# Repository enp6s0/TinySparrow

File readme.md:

# TinySparrow
A compact, low(ish)-cost, CAN-FD enabled *core board* for all sorts of automotive shenanigans (and beyond)!

Ever wanted to integrate CAN bus functionality into your projects, but didn't want to
deal with laying out all the commonly used parts every single time?

Then TinySparrow is for you! Now in its 2nd generation, this cute little board combines a
[STM32G0X1](https://www.st.com/en/microcontrollers-microprocessors/stm32g0x1.html) MCU,
2x CAN-FD transceivers and power regulation all in a single board, ready to be integrated
in all your CAN-enabled device ideas.

### General specifications

* Compact footprint: `32 x 27 mm`

* QFN-48 **STM32G0x1** series ARM Cortex-M0+ microcontroller
	* Ships with [STM32G0B1CBU6](https://www.st.com/en/microcontrollers-microprocessors/stm32g0b1cb.html) by default (128K flash, 144K RAM)
	* Also compatible with [STM32G0C1CEU6](https://www.st.com/en/microcontrollers-microprocessors/stm32g0c1ce.html) should you want more RAM/flash or hardware crypto
	* Crystal-less USB device capability

* Dual CAN-FD (up to 5Mbps)
	* Texas Instruments [TCAN332G](https://www.ti.com/product/TCAN332G) PHYs
	* CAN bus ESD diodes included (probably a good idea to add another near connectors though)

* 2-stage automotive power supply
	* Much wider input range: 5 to 25 VDC in!
	* "Batteries included" protection: reverse polarity and voltage clamping diodes onboard
	* **3.3 VDC system voltage** (~500mA available for extra peripherals)
	* Texas Instruments [LMR43610-Q1](https://www.ti.com/product/LMR43610-Q1) buck converter (first stage)
	* STMicroelectronics [LD49100](https://www.st.com/resource/en/datasheet/ld49100.pdf) linear regulator (second stage)

* 2.54mm "pin grid array" I/O connectors
	* 72 total pins available, 61 currently used (all unused MCU pins available)
	* 11 pins reserved for future use (with other boards/revisions)
	* Easy to solder / design carrier boards for :)

### Module pinout

* Top left corner identified by golden notch
* Pins marked with `x` are reserved for future use (do not connect)

|              |              |             |        |        |        |        |     |     |     |            |            |
|:------------:|:------------:|:-----------:|:------:|:------:|:------:|:------:|:---:|:---:|:---:|:----------:|:----------:|
| Key (no pin) |      GND     |     GND     |    x   |    x   |    x   |    x   | GND |  x  |  x  |      x     |  GND       |
|     PA10     |  USB+ (PA12) | USB- (PA11) | CAN0 H | CAN0 L | CAN1 H | CAN1 L | GND |  x  |  x  |      x     | PB14       |
| nRESET (PF2) |  +3V3 (PROG) |             |        |        |        |        |     |     |     |    PB13    | PB12       |
| SWCLK (PA14) | SWDIO (PA13) |             |        |        |        |        |     |     |     |    PB11    | PB10       |
|      PD2     |     PA15     |             |        |        |        |        |     |     |     |     GND    |  PB2       |
|      PB3     |      PD3     |             |        |        |        |        |     |     |     |    PB15    |  PA8       |
|      PB4     |      PB5     |             |        |        |        |        |     |     |     |     PA9    |  PC6       |
|      PB6     |      PB7     |             |        |        |        |        |     |     |     | Power good |  PC7       |
|      PB8     |      PB9     |     PC13    |  PC15  |  +3V3  |   PF1  |   PA1  | PA3 | PA5 | PA7 |      x     |  GND       |
|      GND     |      GND     |     PC14    |  +VBAT |  +3V3  |   PF0  |   PA0  | PA2 | PA4 | PA6 |     GND    |  +VDC (in) |

### Revision/stepping info

* `A1`: initial release for Gen2 design
* `A2`: ESD diode routing fixes, lighter application of via-in-pad to improve manufacturability *(Breaking pinout change: SWDIO/SWCLK swap, +VDC in moved)*

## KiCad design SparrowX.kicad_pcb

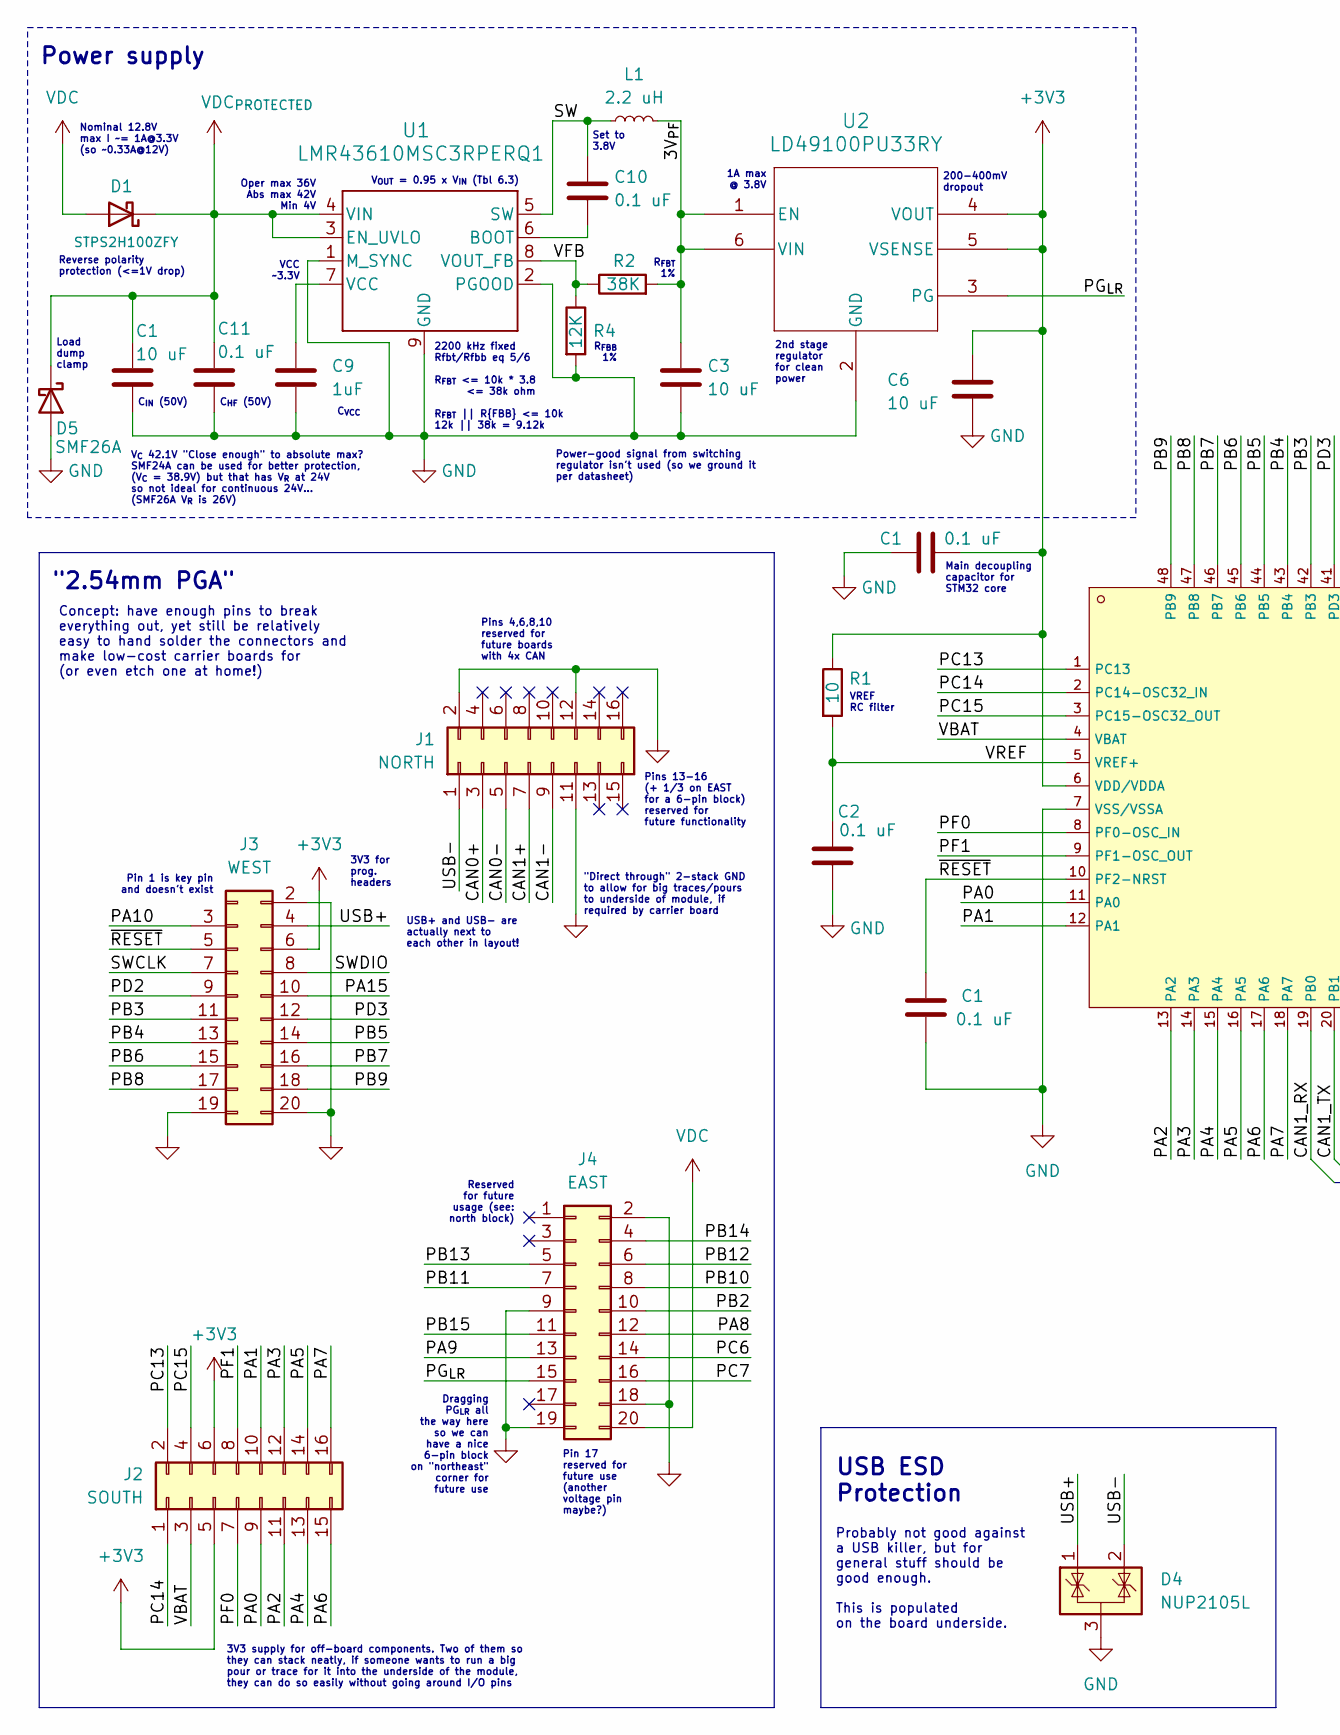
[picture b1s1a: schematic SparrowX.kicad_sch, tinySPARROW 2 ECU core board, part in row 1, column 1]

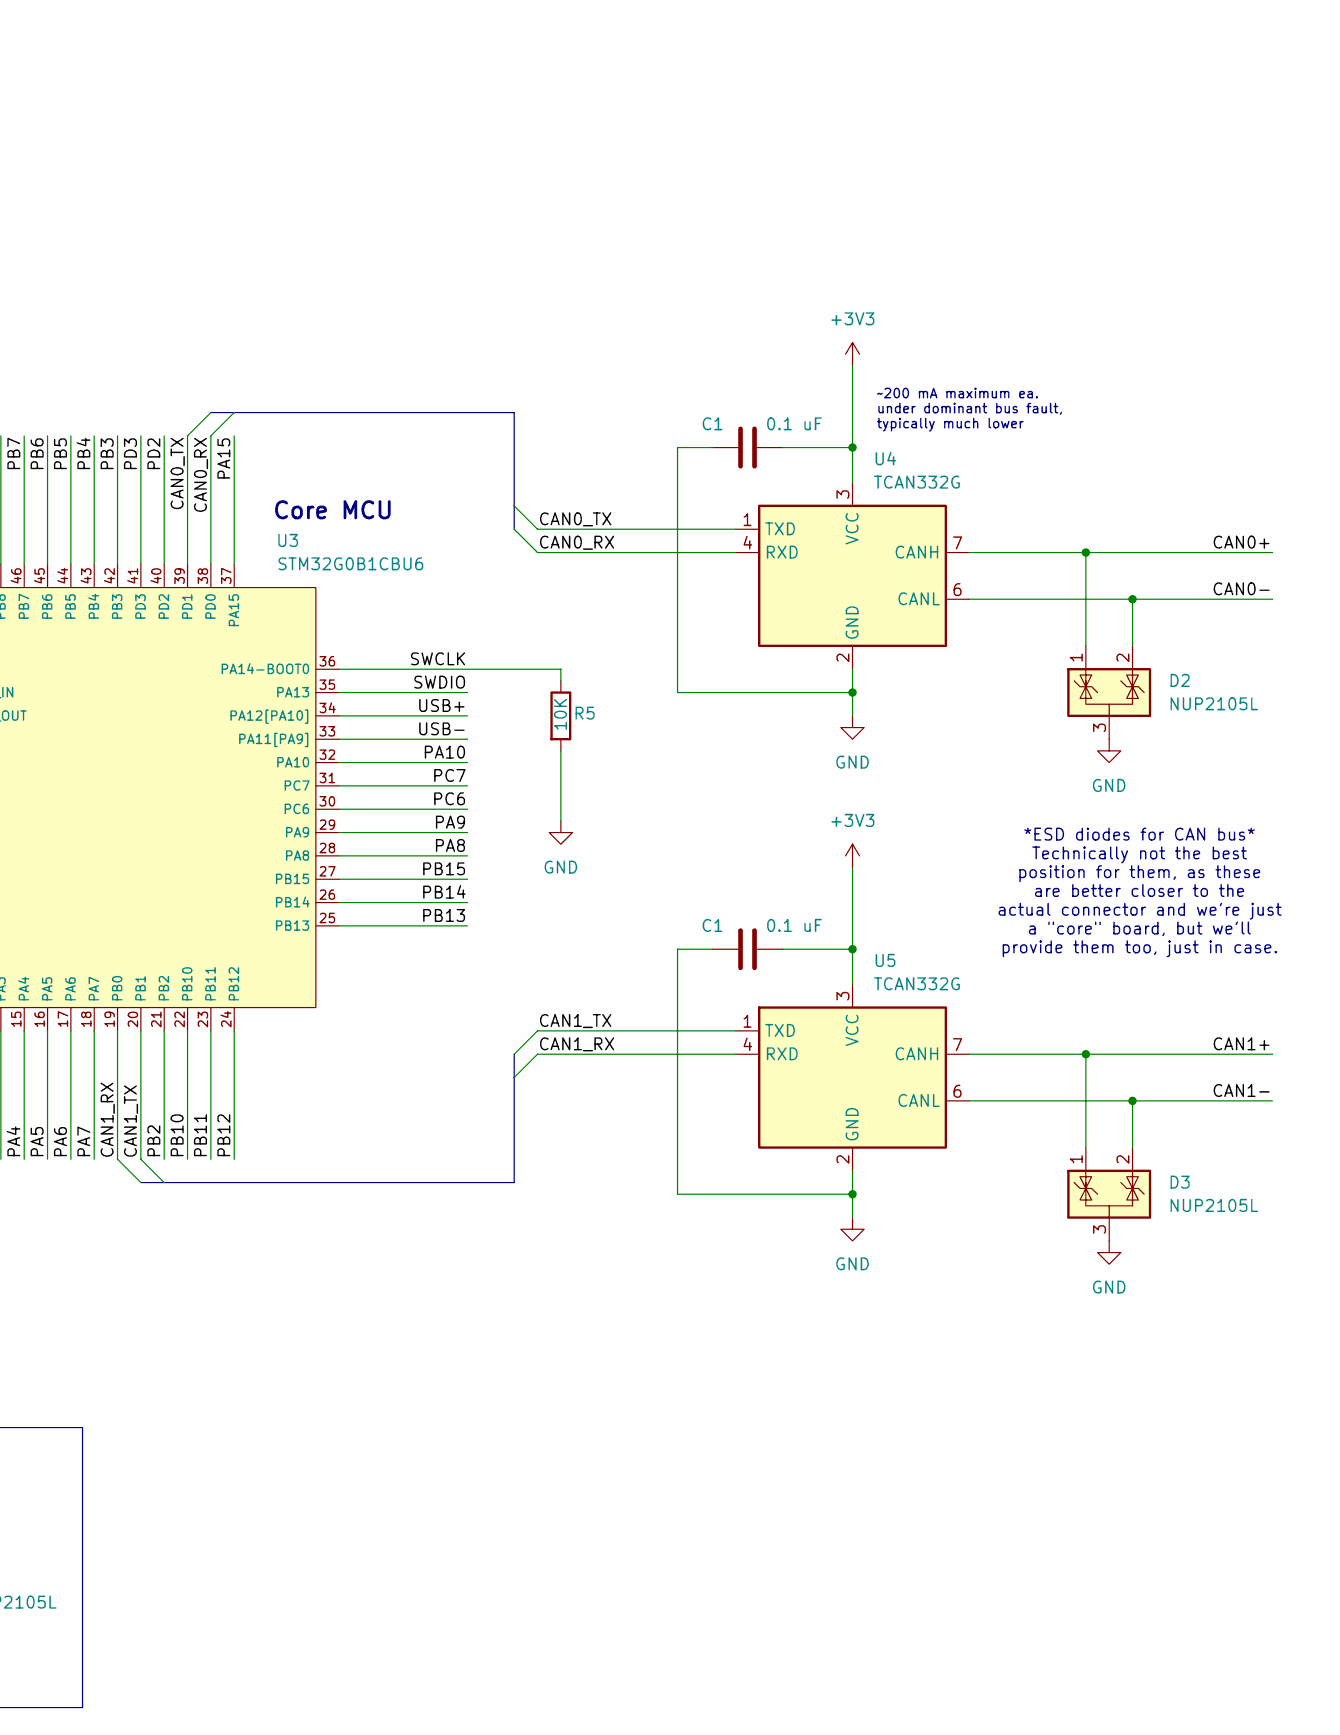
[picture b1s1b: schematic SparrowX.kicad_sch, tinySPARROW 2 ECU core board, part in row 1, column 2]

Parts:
C1, C2, C10, C11: 0.1 uF; C_0402_1005Metric
C3: 10 uF; C_0402_1005Metric; LCSC C377773
C6: 10 uF; C_0805_2012Metric; LCSC C377773
C9: 1uF; C_0402_1005Metric
D1: STPS2H100ZFY; D_SOD-123F
D2, D3, D4: NUP2105L; SOT-23
D5: SMF26A; D_SOD-123F
J1: NORTH; PinHeader_2x08_P2.54mm_Vertical
J2: SOUTH; PinHeader_2x08_P2.54mm_Vertical
J3: WEST; PinHeader_2x10_P2.54mm_Vertical
J4: EAST; PinHeader_2x10_P2.54mm_Vertical
L1: 2.2 uH; L_0805_2012Metric
R1: 10; R_0402_1005Metric
R2: 38K; R_0402_1005Metric
R4: 12K; R_0402_1005Metric
R5: 10K; R_0402_1005Metric
U1: LMR43610MSC3RPERQ1; RPE0009A-MFG
U2: LD49100PU33RY; DFN6_LD49100_STM
U3: STM32G0B1CBU6; QFN-48-1EP_7x7mm_P0.5mm_EP5.6x5.6mm; LCSC C2847904
U4, U5: TCAN332G; SOT-23-8

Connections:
/3V_{PF}: C3.1, L1.2, R2.2, U2.1 (EN), U2.6 (VIN)
/CAN0+: D2.1 (K), J1.3, U4.7 (CANH)
/CAN0-: D2.2 (K), J1.5, U4.6 (CANL)
/CAN0_RX: U3.38 (PD0), U4.4 (RXD)
/CAN0_TX: U3.39 (PD1), U4.1 (TXD)
/CAN1+: D3.1 (K), J1.7, U5.7 (CANH)
/CAN1-: D3.2 (K), J1.9, U5.6 (CANL)
/CAN1_RX: U3.19 (PB0), U5.4 (RXD)
/CAN1_TX: U3.20 (PB1), U5.1 (TXD)
/PA0: J2.9, U3.11 (PA0)
/PA1: J2.10, U3.12 (PA1)
/PA2: J2.11, U3.13 (PA2)
/PA3: J2.12, U3.14 (PA3)
/PA4: J2.13, U3.15 (PA4)
/PA5: J2.14, U3.16 (PA5)
/PA6: J2.15, U3.17 (PA6)
/PA7: J2.16, U3.18 (PA7)
/PA8: J4.12, U3.28 (PA8)
/PA9: J4.13, U3.29 (PA9)
/PA10: J3.3, U3.32 (PA10)
/PA15: J3.10, U3.37 (PA15)
/PB2: J4.10, U3.21 (PB2)
/PB3: J3.11, U3.42 (PB3)
/PB4: J3.13, U3.43 (PB4)
/PB5: J3.14, U3.44 (PB5)
/PB6: J3.15, U3.45 (PB6)
/PB7: J3.16, U3.46 (PB7)
/PB8: J3.17, U3.47 (PB8)
/PB9: J3.18, U3.48 (PB9)
/PB10: J4.8, U3.22 (PB10)
/PB11: J4.7, U3.23 (PB11)
/PB12: J4.6, U3.24 (PB12)
/PB13: J4.5, U3.25 (PB13)
/PB14: J4.4, U3.26 (PB14)
/PB15: J4.11, U3.27 (PB15)
/PC6: J4.14, U3.30 (PC6)
/PC7: J4.16, U3.31 (PC7)
/PC13: J2.2, U3.1 (PC13)
/PC14: J2.1, U3.2 (PC14-OSC32_IN)
/PC15: J2.4, U3.3 (PC15-OSC32_OUT)
/PD2: J3.9, U3.40 (PD2)
/PD3: J3.12, U3.41 (PD3)
/PF0: J2.7, U3.8 (PF0-OSC_IN)
/PF1: J2.8, U3.9 (PF1-OSC_OUT)
/PG_{LR}: J4.15, U2.3 (PG)
/SW: C10.2, L1.1, U1.5 (SW)
/SWCLK: J3.7, R5.1, U3.36 (PA14-BOOT0)
/SWDIO: J3.8, U3.35 (PA13)
/USB+: D4.1 (K), J3.4, U3.34 (PA12[PA10])
/USB-: D4.2 (K), J1.1, U3.33 (PA11[PA9])
/VBAT: J2.3, U3.4 (VBAT)
/VFB: R2.1, R4.1, U1.8 (VOUT_FB)
/VREF: C2.1, R1.2, U3.5 (VREF+)
GND: C1.2, C2.2, C3.2, C6.2, C9.2, C11.2, D2.3 (A), D3.3 (A), D4.3 (A), D5.2 (A), J1.2, J1.11, J1.12, J3.2, J3.19, J3.20, J4.2, J4.9, J4.18, J4.19, R4.2, R5.2, U1.1 (M_SYNC), U1.2 (PGOOD), U1.9 (GND), U2.2 (GND), U2.7 (EPAD), U3.7 (VSS/VSSA), U3.49 (GND_PAD), U4.2 (GND), U5.2 (GND); also elsewhere on the board
unnamed: C10.1, U1.6 (BOOT)
unnamed: C9.1, U1.7 (VCC)
VDC: D1.2 (A), J4.20

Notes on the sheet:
1A max @ 3.8V
Main decoupling capacitor for STM32 core
2200 kHz fixed Rfbt/Rfbb eq 5/6 R_{FBT} <= 10k * 3.8 <= 38k ohm R_{FBT} || R{FBB} <= 10k 12k || 38k = 9.12k
"Direct through" 2-stack GND to allow for big traces/pours to underside of module, if required by carrier board
VCC ~3.3V
~200 mA maximum ea. under dominant bus fault, typically much lower
2nd stage regulator for clean power
Pin 17 reserved for future use (another voltage pin maybe?)
Concept: have enough pins to break everything out, yet still be relatively easy to hand solder the connectors and make low-cost carrier boards for (or even etch one at home!)
Power-good signal from switching regulator isn't used (so we ground it per datasheet)
R_{FBB} 1%
V_{C} 42.1V "Close enough" to absolute max? SMF24A can be used for better protection, (V_{C} = 38.9V) but that has V_{R} at 24V so not ideal for continuous 24V... (SMF26A V_{R} is 26V)
VREF RC filter
Power supply
Set to 3.8V
USB ESD Protection
*ESD diodes for CAN bus* Technically not the best position for them, as these are better closer to the actual connector and we're just a "core" board, but we'll provide them too, just in case.
Load dump clamp
Dragging PG_{LR} all the way here so we can have a nice 6-pin block on "northeast" corner for future use
3V3 for prog. headers
Reverse polarity protection (<=1V drop)
200-400mV dropout
Pins 13-16 (+ 1/3 on EAST for a 6-pin block) reserved for future functionality
Core MCU
"2.54mm PGA"
Probably not good against a USB killer, but for general stuff should be good enough. This is populated on the board underside.
Pin 1 is key pin and doesn't exist
R_{FBT} 1%
USB+ and USB- are actually next to each other in layout!
Pins 4,6,8,10 reserved for future boards with 4x CAN
Nominal 12.8V max I ~= 1A@3.3V (so ~0.33A@12V)
C_{HF} (50V)
Reserved for future usage (see: north block)
3V3 supply for off-board components. Two of them so they can stack neatly, if someone wants to run a big pour or trace for it into the underside of the module, they can do so easily without going around I/O pins
V_{OUT} = 0.95 x V_{IN} (Tbl 6.3)
C_{IN} (50V)
C_{VCC}
Oper max 36V Abs max 42V Min 4V

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
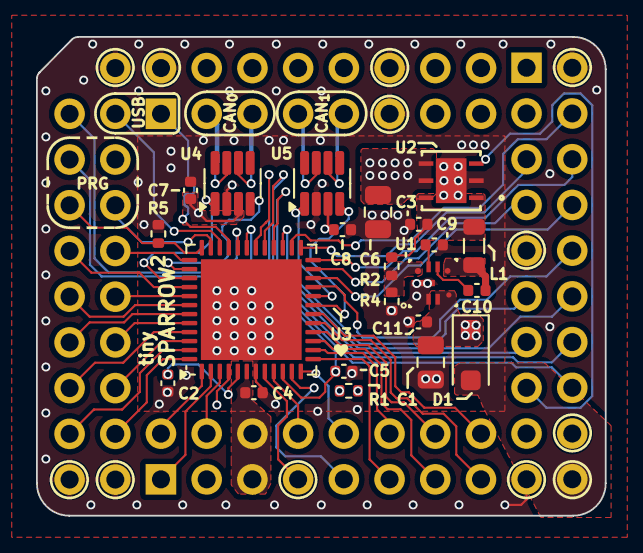
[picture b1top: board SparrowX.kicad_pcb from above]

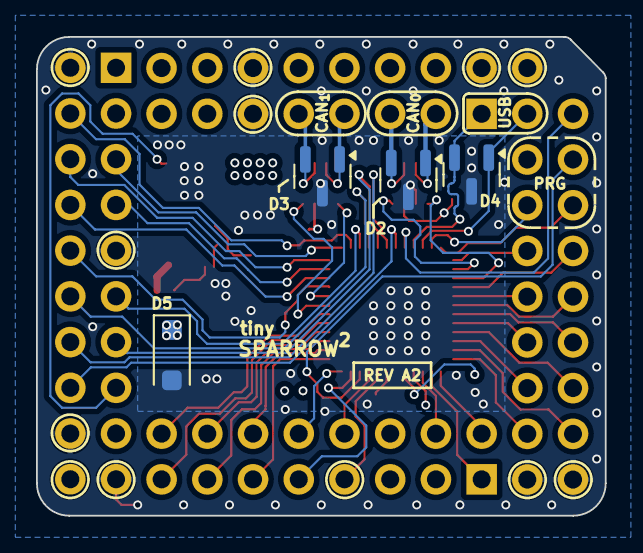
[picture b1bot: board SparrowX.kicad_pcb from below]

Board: 4 copper layers, 31.6 x 26.6 mm, 30 parts (4 on the bottom side), 60 nets.

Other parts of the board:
C4, C5, C7, C8: 0.1 uF; C_0402_1005Metric

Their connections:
GND: C4.2, C5.2, C7.2, C8.2; also elsewhere on the board

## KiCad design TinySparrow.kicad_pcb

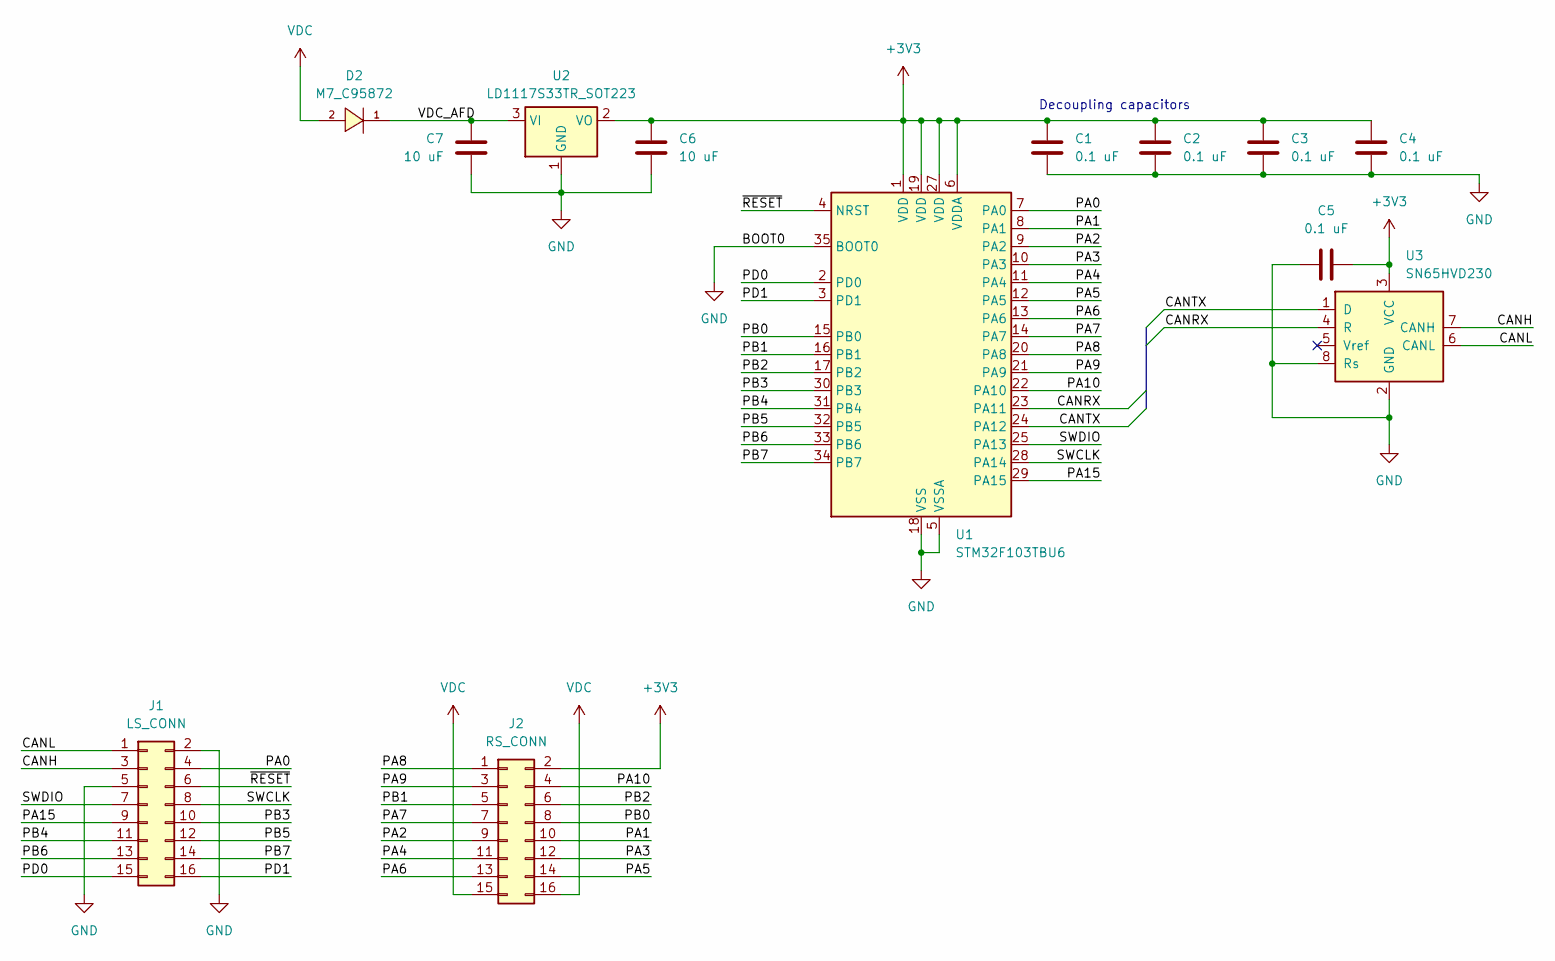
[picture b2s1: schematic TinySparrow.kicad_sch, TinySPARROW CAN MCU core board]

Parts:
C1, C2, C3, C4, C5: 0.1 uF; C_0603_1608Metric
C6: 10 uF; C_0805_2012Metric; LCSC C377773
C7: 10 uF; C_0805_2012Metric
D2: M7_C95872; SMA_L4.3-W2.6-LS5.2-RD; LCSC C95872
J1: LS_CONN; PinSocket_2x08_P2.54mm_Vertical
J2: RS_CONN; PinSocket_2x08_P2.54mm_Vertical
U1: STM32F103TBU6; QFN-36-1EP_6x6mm_P0.5mm_EP4.1x4.1mm
U2: LD1117S33TR_SOT223; SOT-223-3_TabPin2; LCSC C71121
U3: SN65HVD230; SOIC-8_3.9x4.9mm_P1.27mm

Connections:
+3V3: C1.2, C2.2, C3.2, C4.2, C5.1, C6.1, J2.2, U1.1 (VDD), U1.6 (VDDA), U1.19 (VDD), U1.27 (VDD), U2.2 (VO), U3.3 (VCC)
/CANH: J1.3, U3.7 (CANH)
/CANL: J1.1, U3.6 (CANL)
/CANRX: U1.23 (PA11), U3.4 (R)
/CANTX: U1.24 (PA12), U3.1 (D)
/PA0: J1.4, U1.7 (PA0)
/PA1: J2.10, U1.8 (PA1)
/PA2: J2.9, U1.9 (PA2)
/PA3: J2.12, U1.10 (PA3)
/PA4: J2.11, U1.11 (PA4)
/PA5: J2.14, U1.12 (PA5)
/PA6: J2.13, U1.13 (PA6)
/PA7: J2.7, U1.14 (PA7)
/PA8: J2.1, U1.20 (PA8)
/PA9: J2.3, U1.21 (PA9)
/PA10: J2.4, U1.22 (PA10)
/PA15: J1.9, U1.29 (PA15)
/PB0: J2.8, U1.15 (PB0)
/PB1: J2.5, U1.16 (PB1)
/PB2: J2.6, U1.17 (PB2)
/PB3: J1.10, U1.30 (PB3)
/PB4: J1.11, U1.31 (PB4)
/PB5: J1.12, U1.32 (PB5)
/PB6: J1.13, U1.33 (PB6)
/PB7: J1.14, U1.34 (PB7)
/PD0: J1.15, U1.2 (PD0)
/PD1: J1.16, U1.3 (PD1)
/SWCLK: J1.8, U1.28 (PA14)
/SWDIO: J1.7, U1.25 (PA13)
/VDC_AFD: C7.2, U2.3 (VI); also elsewhere on the board
/~RESET: J1.6, U1.4 (NRST)
GND: C1.1, C2.1, C3.1, C4.1, C5.2, C6.2, C7.1, J1.2, J1.5, U1.5 (VSSA), U1.18 (VSS), U1.26 (VSS), U1.35 (BOOT0), U1.36 (VSS), U1.37 (VSS), U2.1 (GND), U3.2 (GND), U3.8 (Rs)
VDC: J2.15, J2.16; also elsewhere on the board

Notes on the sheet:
Decoupling capacitors

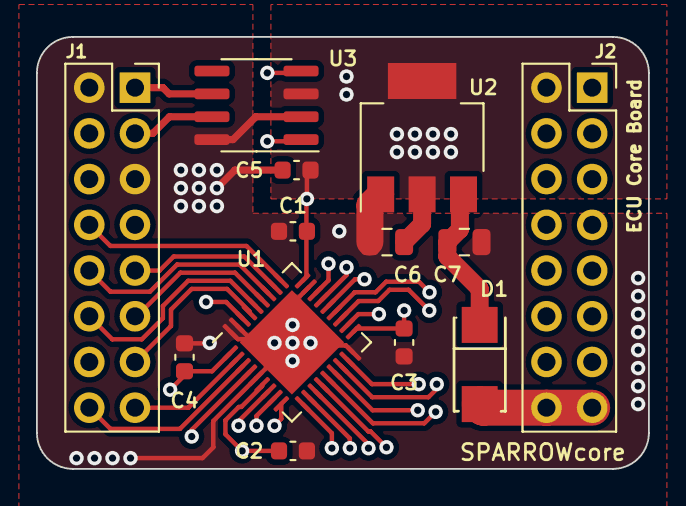
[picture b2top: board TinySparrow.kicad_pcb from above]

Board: 6 copper layers, 34.0 x 24.0 mm, 13 parts (0 on the bottom side), 33 nets.

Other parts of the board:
D1: M7_C95872; SMA_L4.3-W2.6-LS5.2-RD

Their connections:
/VDC_AFD: D1.1 (K); also elsewhere on the board
VDC: D1.2 (A); also elsewhere on the board

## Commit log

2024-02-19 Initial push
2024-02-19 Typo fix
2024-02-19 Add OHL-P
2024-02-19 Oops
2024-02-23 Add link to breadboard adapter
2024-04-10 Update carrier board requirements in README
2024-04-10 WIP: next generation TinySparrow with STM32G431 and CAN-FD
2024-11-23 NextGen: MCU upgrade to STM32G473CBT6
2025-11-27 WIP: Next generation TinySparrow
2025-11-27 Everybody gets more vias!
2025-11-27 Add pinout table
2025-11-27 Oops: fix missing PF0 pin
2025-11-27 Cortex-M0+, not M0
2025-11-27 Move power good signal pin for better layout
2025-11-27 Nudge U2/C3 up a bit to make 3V3 zone wider
2025-11-27 Oops: move silkscreen text away from pads
2025-11-27 Routing tweaks
2025-11-29 Add VREF+ RC-filter; silkscreen adjustments
2025-11-29 Tie power good pin of TPS629210 to GND (see datasheet section 8.3.5)
2025-11-29 WIP: new switching regulator
2025-11-29 PSU P1 migration done!
2025-11-29 Formalizing the contributors list :)
2025-11-29 Update board rendering
2025-11-29 Via tweaks
2025-11-29 Give USB some solid ground underneath
2025-11-29 Left-side +3V3 is for programming use
2025-11-29 More silkscreen tweaks
2025-11-29 Add board stepping/revision silkscreen
2025-11-29 Schematic comment touch-ups
2025-11-29 README touchup
2025-12-01 Oops: didn't update this after adding power good pin...
2025-12-03 Silkscreen tweak: align reference designators
2025-12-03 More README touchups
2025-12-03 Add revision info to README
2025-12-06 C9 doesn't have to be 50V
2025-12-06 DFM: get rid of 0201 SMD components
2025-12-11 Silkscreen: fix 'double-C1' problem
2025-12-11 A2 revision
2025-12-11 Rev A2: add module corner key, silkscreen tweaks
2025-12-11 Rev A2: add module corner key, silkscreen tweaks, move +VDC in
2025-12-11 Widen +VBAT trace a bit
